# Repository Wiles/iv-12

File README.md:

# iv-12

File for the case are available at: https://www.thingiverse.com/thing:4103417

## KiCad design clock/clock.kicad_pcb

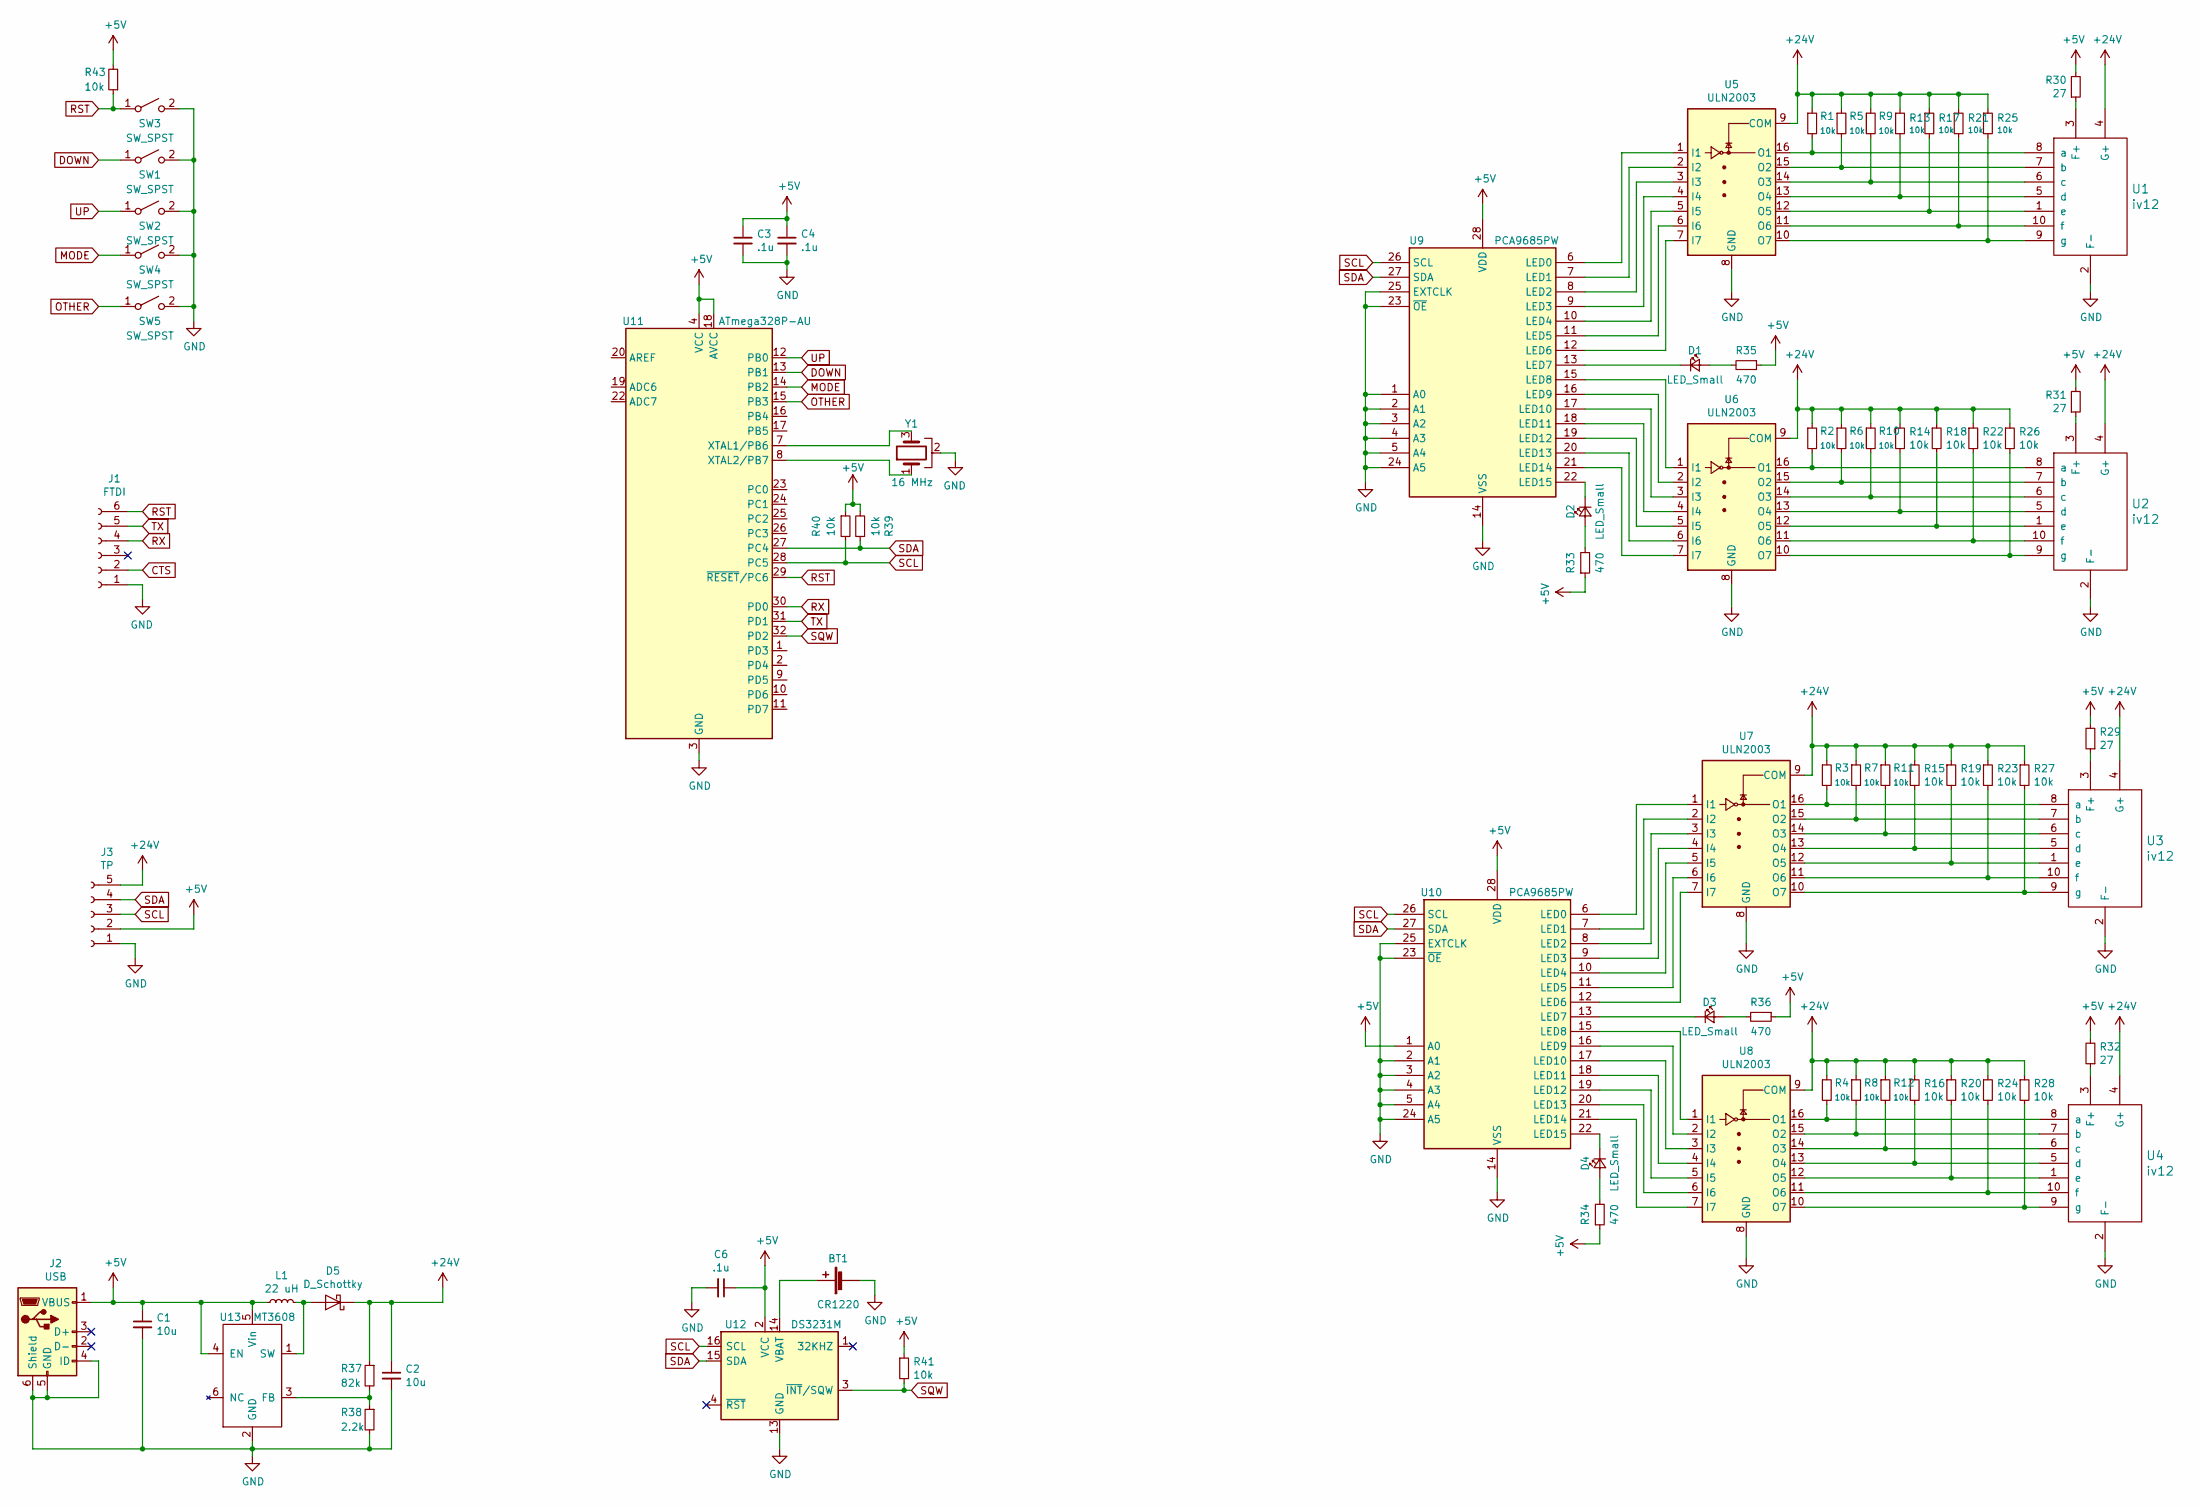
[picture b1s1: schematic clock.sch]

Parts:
BT1: CR1220; BatteryHolder_Keystone_3000_1x12mm
C1, C2: 10u; C_1206_3216Metric_Pad1.42x1.75mm_HandSolder
C3, C4, C6: .1u; C_0603_1608Metric_Pad1.05x0.95mm_HandSolder
D1, D2, D3, D4: LED_Small; LED_0805_2012Metric_Pad1.15x1.40mm_HandSolder
D5: D_Schottky; D_SMA
J1: FTDI; PinHeader_1x06_P2.54mm_Vertical
J2: USB; USB_Micro-B_Wuerth_614105150721_Vertical
J3: TP; PinHeader_1x05_P2.54mm_Vertical
L1: 22 uH; L_10.4x10.4_H4.8
R1, R2, R3, R4, R5, R6, R7, R8, R9, R10, R11, R12, R13, R14, R15, R16, R17, R18, R19, R20, R21, R22, R23, R24, R25, R26, R27, R28, R39, R40, R41, R43: 10k; R_0603_1608Metric_Pad1.05x0.95mm_HandSolder
R29, R30, R31, R32: 27; R_0603_1608Metric_Pad1.05x0.95mm_HandSolder
R33, R34, R35, R36: 470; R_0603_1608Metric_Pad1.05x0.95mm_HandSolder
R37: 82k; R_0603_1608Metric_Pad1.05x0.95mm_HandSolder
R38: 2.2k; R_0603_1608Metric_Pad1.05x0.95mm_HandSolder
SW1, SW2, SW3, SW4, SW5: SW_SPST; SW_SPST_TL3342
U1, U2, U3, U4: iv12; iv12-large
U5, U6, U7, U8: ULN2003; SOIC-16_3.9x9.9mm_P1.27mm
U9, U10: PCA9685PW; TSSOP-28_4.4x9.7mm_P0.65mm
U11: ATmega328P-AU; TQFP-32_7x7mm_P0.8mm
U12: DS3231M; SOIC-16W_7.5x10.3mm_P1.27mm
U13: MT3608; SOT-23-6_Handsoldering
Y1: 16 MHz; Resonator_SMD_muRata_CSTxExxV-3Pin_3.0x1.1mm_HandSoldering

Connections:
+5V: C1.1, C3.1, C4.1, C6.1, J1.3, J2.1 (VBUS), J3.2, L1.1, R29.2, R30.2, R31.2, R32.2, R33.1, R34.1, R35.1, R36.1, R39.2, R40.1, R41.1, R43.2, U9.28 (VDD), U10.1 (A0), U10.28 (VDD), U11.4 (VCC), U11.6 (VCC), U11.18 (AVCC), U12.2 (VCC), U13.4 (EN), U13.5 (Vin)
+24V: C2.1, D5.1 (K), J3.5, R1.1, R2.1, R3.1, R4.1, R5.1, R6.1, R7.1, R8.1, R9.1, R10.1, R11.1, R12.1, R13.1, R14.1, R15.1, R16.1, R17.1, R18.1, R19.1, R20.1, R21.1, R22.1, R23.1, R24.1, R25.1, R26.1, R27.1, R28.1, R37.1, U1.4 (G+), U2.4 (G+), U3.4 (G+), U4.4 (G+), U5.9 (COM), U6.9 (COM), U7.9 (COM), U8.9 (COM)
CTS: J1.2
DOWN: SW1.1 (A), U11.13 (PB1)
GND: BT1.2 (-), C1.2, C2.2, C3.2, C4.2, C6.2, J1.1, J2.4 (ID), J2.5 (GND), J2.6 (Shield), J3.1, R38.2, SW1.2 (B), SW2.2 (B), SW3.2 (B), SW4.2 (B), SW5.2 (B), U1.2 (F-), U2.2 (F-), U3.2 (F-), U4.2 (F-), U5.8 (GND), U6.8 (GND), U7.8 (GND), U8.8 (GND), U9.1 (A0), U9.2 (A1), U9.3 (A2), U9.4 (A3), U9.5 (A4), U9.14 (VSS), U9.23 (~OE), U9.24 (A5), U9.25 (EXTCLK), U10.2 (A1), U10.3 (A2), U10.4 (A3), U10.5 (A4), U10.14 (VSS), U10.23 (~OE), U10.24 (A5), U10.25 (EXTCLK), U11.3 (GND), U11.5 (GND), U11.21 (GND), U12.5 (GND), U12.6 (GND), U12.7 (GND), U12.8 (GND), U12.9 (GND), U12.10 (GND), U12.11 (GND), U12.12 (GND), U12.13 (GND), U13.2 (GND), Y1.2
MODE: SW4.1 (A), U11.14 (PB2)
unnamed: BT1.1 (+), U12.14 (VBAT)
unnamed: D1.1 (K), U9.13 (LED7)
unnamed: D1.2 (A), R35.2
unnamed: D2.1 (K), U9.22 (LED15)
unnamed: D2.2 (A), R33.2
unnamed: D3.1 (K), U10.13 (LED7)
unnamed: D3.2 (A), R36.2
unnamed: D4.1 (K), U10.22 (LED15)
unnamed: D4.2 (A), R34.2
unnamed: D5.2 (A), L1.2, U13.1 (SW)
unnamed: R1.2, U1.8 (a), U5.16 (O1)
unnamed: R2.2, U2.8 (a), U6.16 (O1)
unnamed: R3.2, U3.8 (a), U7.16 (O1)
unnamed: R4.2, U4.8 (a), U8.16 (O1)
unnamed: R5.2, U1.7 (b), U5.15 (O2)
unnamed: R6.2, U2.7 (b), U6.15 (O2)
unnamed: R7.2, U3.7 (b), U7.15 (O2)
unnamed: R8.2, U4.7 (b), U8.15 (O2)
unnamed: R9.2, U1.6 (c), U5.14 (O3)
unnamed: R10.2, U2.6 (c), U6.14 (O3)
unnamed: R11.2, U3.6 (c), U7.14 (O3)
unnamed: R12.2, U4.6 (c), U8.14 (O3)
unnamed: R13.2, U1.5 (d), U5.13 (O4)
unnamed: R14.2, U2.5 (d), U6.13 (O4)
unnamed: R15.2, U3.5 (d), U7.13 (O4)
unnamed: R16.2, U4.5 (d), U8.13 (O4)
unnamed: R17.2, U1.1 (e), U5.12 (O5)
unnamed: R18.2, U2.1 (e), U6.12 (O5)
unnamed: R19.2, U3.1 (e), U7.12 (O5)
unnamed: R20.2, U4.1 (e), U8.12 (O5)
unnamed: R21.2, U1.10 (f), U5.11 (O6)
unnamed: R22.2, U2.10 (f), U6.11 (O6)
unnamed: R23.2, U3.10 (f), U7.11 (O6)
unnamed: R24.2, U4.10 (f), U8.11 (O6)
unnamed: R25.2, U1.9 (g), U5.10 (O7)
unnamed: R26.2, U2.9 (g), U6.10 (O7)
unnamed: R27.2, U3.9 (g), U7.10 (O7)
unnamed: R28.2, U4.9 (g), U8.10 (O7)
unnamed: R29.1, U3.3 (F+)
unnamed: R30.1, U1.3 (F+)
unnamed: R31.1, U2.3 (F+)
unnamed: R32.1, U4.3 (F+)
unnamed: R37.2, R38.1, U13.3 (FB)
unnamed: U5.1 (I1), U9.6 (LED0)
unnamed: U5.2 (I2), U9.7 (LED1)
unnamed: U5.3 (I3), U9.8 (LED2)
unnamed: U5.4 (I4), U9.9 (LED3)
unnamed: U5.5 (I5), U9.10 (LED4)
unnamed: U5.6 (I6), U9.11 (LED5)
unnamed: U5.7 (I7), U9.12 (LED6)
unnamed: U6.1 (I1), U9.15 (LED8)
unnamed: U6.2 (I2), U9.16 (LED9)
unnamed: U6.3 (I3), U9.17 (LED10)
unnamed: U6.4 (I4), U9.18 (LED11)
unnamed: U6.5 (I5), U9.19 (LED12)
unnamed: U6.6 (I6), U9.20 (LED13)
unnamed: U6.7 (I7), U9.21 (LED14)
unnamed: U7.1 (I1), U10.6 (LED0)
unnamed: U7.2 (I2), U10.7 (LED1)
unnamed: U7.3 (I3), U10.8 (LED2)
unnamed: U7.4 (I4), U10.9 (LED3)
unnamed: U7.5 (I5), U10.10 (LED4)
unnamed: U7.6 (I6), U10.11 (LED5)
unnamed: U7.7 (I7), U10.12 (LED6)
unnamed: U8.1 (I1), U10.15 (LED8)
unnamed: U8.2 (I2), U10.16 (LED9)
unnamed: U8.3 (I3), U10.17 (LED10)
unnamed: U8.4 (I4), U10.18 (LED11)
unnamed: U8.5 (I5), U10.19 (LED12)
unnamed: U8.6 (I6), U10.20 (LED13)
unnamed: U8.7 (I7), U10.21 (LED14)
unnamed: U11.7 (XTAL1/PB6), Y1.3
unnamed: U11.8 (XTAL2/PB7), Y1.1
OTHER: SW5.1 (A), U11.15 (PB3)
RX: J1.4, U11.30 (PD0)
SCL: J3.3, R40.2, U9.26 (SCL), U10.26 (SCL), U11.28 (PC5), U12.16 (SCL)
SDA: J3.4, R39.1, U9.27 (SDA), U10.27 (SDA), U11.27 (PC4), U12.15 (SDA)
SQW: R41.2, U11.32 (PD2), U12.3 (~INT~/SQW)
TX: J1.5, U11.31 (PD1)
UP: SW2.1 (A), U11.12 (PB0)

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
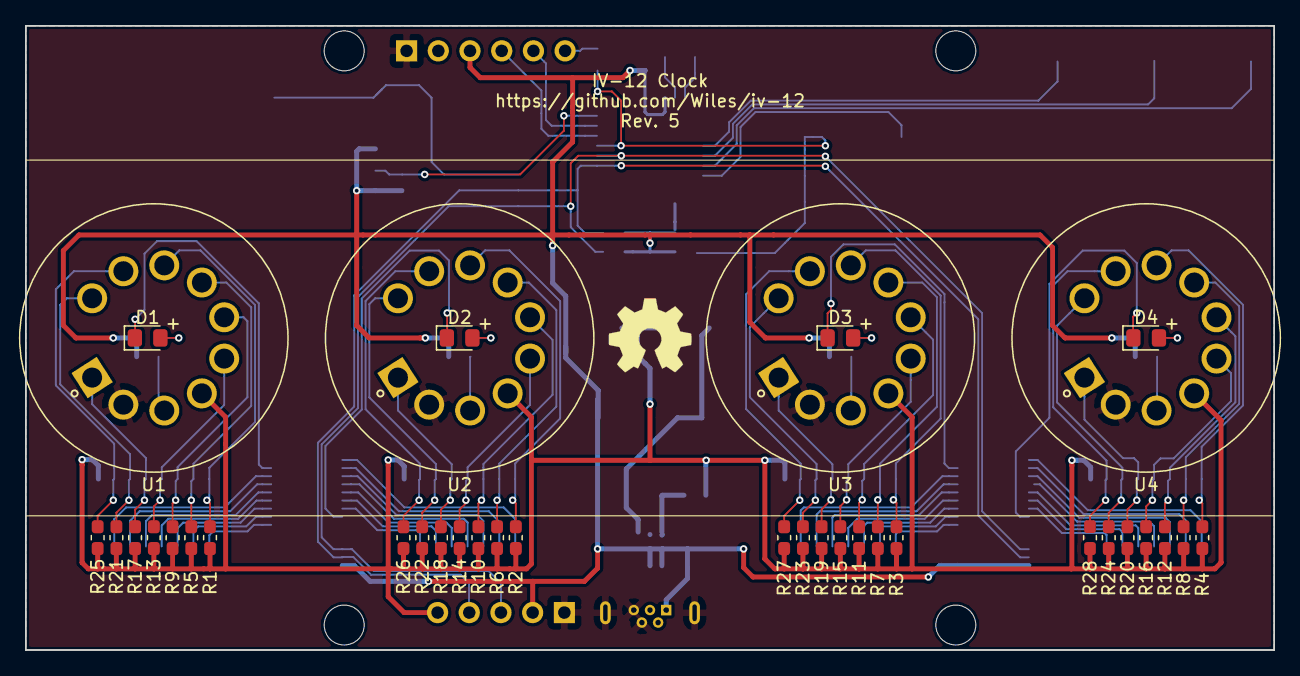
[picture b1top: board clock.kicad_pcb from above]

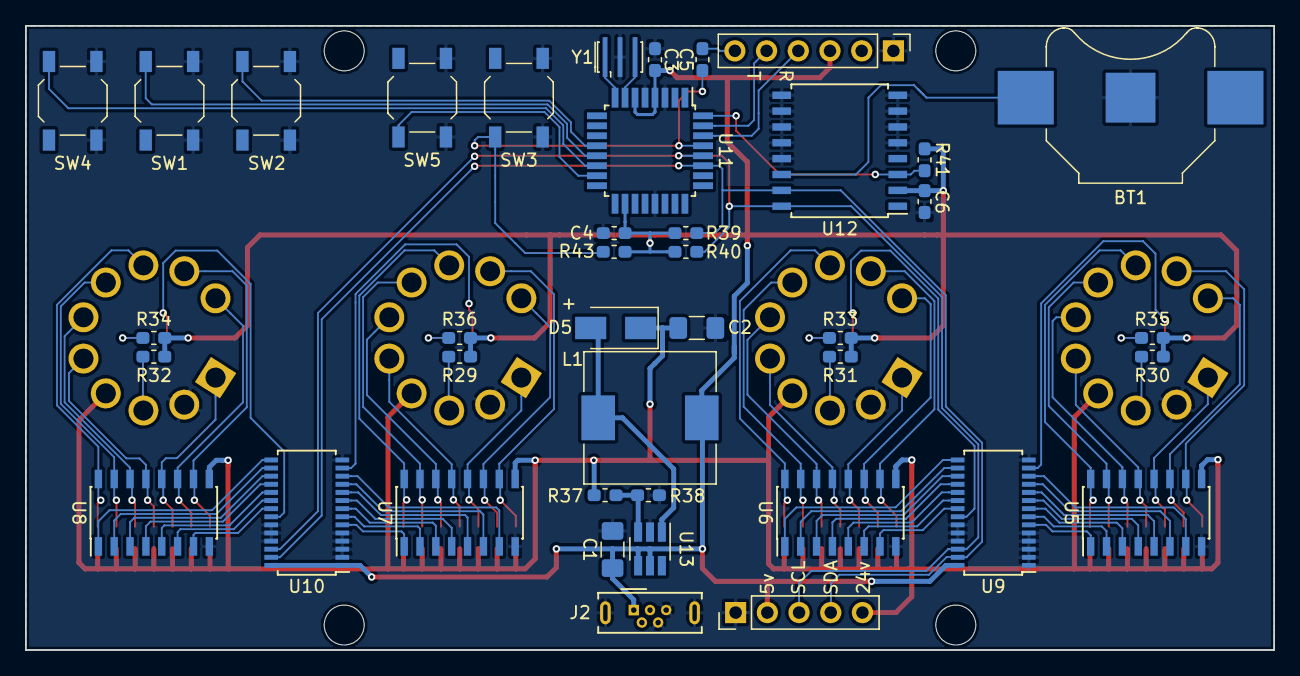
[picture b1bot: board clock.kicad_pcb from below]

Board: 2 copper layers, 100.0 x 50.0 mm, 77 parts (41 on the bottom side), 87 nets.

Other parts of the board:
C5: 1u; C_0603_1608Metric_Pad1.05x0.95mm_HandSolder

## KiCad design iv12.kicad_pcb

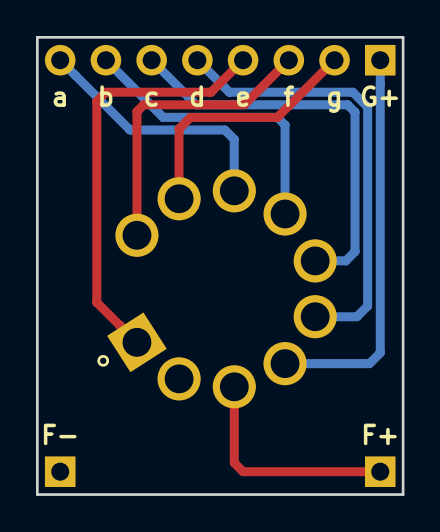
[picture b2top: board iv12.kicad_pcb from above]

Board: 2 copper layers, 20.3 x 25.4 mm, 4 parts (0 on the bottom side), 10 nets.

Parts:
J1: CONN_01X08; Pin_Header_Straight_1x08_Pitch2.54mm
J2, J3: CONN_01X01; Pin_Header_Straight_1x01_Pitch2.54mm
U1: iv12; iv12-large

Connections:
+1V5: J3.1, U1.3
+24V: J1.1, U1.4
GND: J2.1, U1.2
unnamed: J1.2, U1.9
unnamed: J1.3, U1.10
unnamed: J1.4, U1.1
unnamed: J1.5, U1.5
unnamed: J1.6, U1.6
unnamed: J1.7, U1.7
unnamed: J1.8, U1.8

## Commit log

2018-02-23 Breakout board for iv-12 tube
2018-02-24 Renamed filament ground pin to F-
2018-02-25 Start of clock circuit
2018-02-25 Start of power design
2018-02-25 Arduino code playing around with RTC and HV5812 based display
2018-02-27 Added SVG of current layout
2018-02-27 Moved around power features
2018-03-15 Breakout board rev 2. Improved input and used larger holes for tube.
2018-03-15 Files missed from last commit.
2018-03-15 Made labels for segments lowercase to reduce confusion it G and G+
2018-12-02 Rev 1 of clock display board
2018-12-02 Schematic files for clock display pcb
2018-12-31 Clock rev 2 with controller
2019-01-27 Rev 3 pcb
2019-01-27 Fixed silkscreen
2019-02-18 Rev 4 PCB
2019-02-18 Readded OSHW logo
2019-02-19 Layout cleanup
2019-02-19 Hooked up SQW from RTC to MCU
2019-02-19 More cleanup
2019-02-19 Moved 24v test point
2019-02-24 Added diode polarity marks
2019-02-24 Fixed D5 mark layer
2019-02-25 Clean up
2019-03-17 initial code
2019-03-17 Fixed crystal pinout
2019-03-22 Changed USB footprint
2019-03-22 Label Tx and Rx pins
2019-03-25 Added capacitor to reset line
2019-03-25 Refilled zones
2019-03-26 Fixed C3 and C5 labels
2019-03-26 Rev 5 PCB
2019-07-04 Rev 1 firmware
2019-07-09 Added 12/24 hour modes
2019-07-09 Code cleanup
2019-07-12 Swapped plus and minus button
2019-09-14 Cleaned up 12/24 time implementatio
2020-01-08 Added image to repo
2020-01-08 Added image to README
2020-01-14 Added link to thingiverse page to README
